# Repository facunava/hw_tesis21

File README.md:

View this project on [CADLAB.io](https://cadlab.io/project/24727). 

# hw_tesis21
Repositorio dedicado al desarrollo de hardware para la materia Proyecto final en Ingeniería Electrónica, en la casa de estudios Universidad Tecnológica Nacional Regional de Córdoba. [Grupo6/2021]

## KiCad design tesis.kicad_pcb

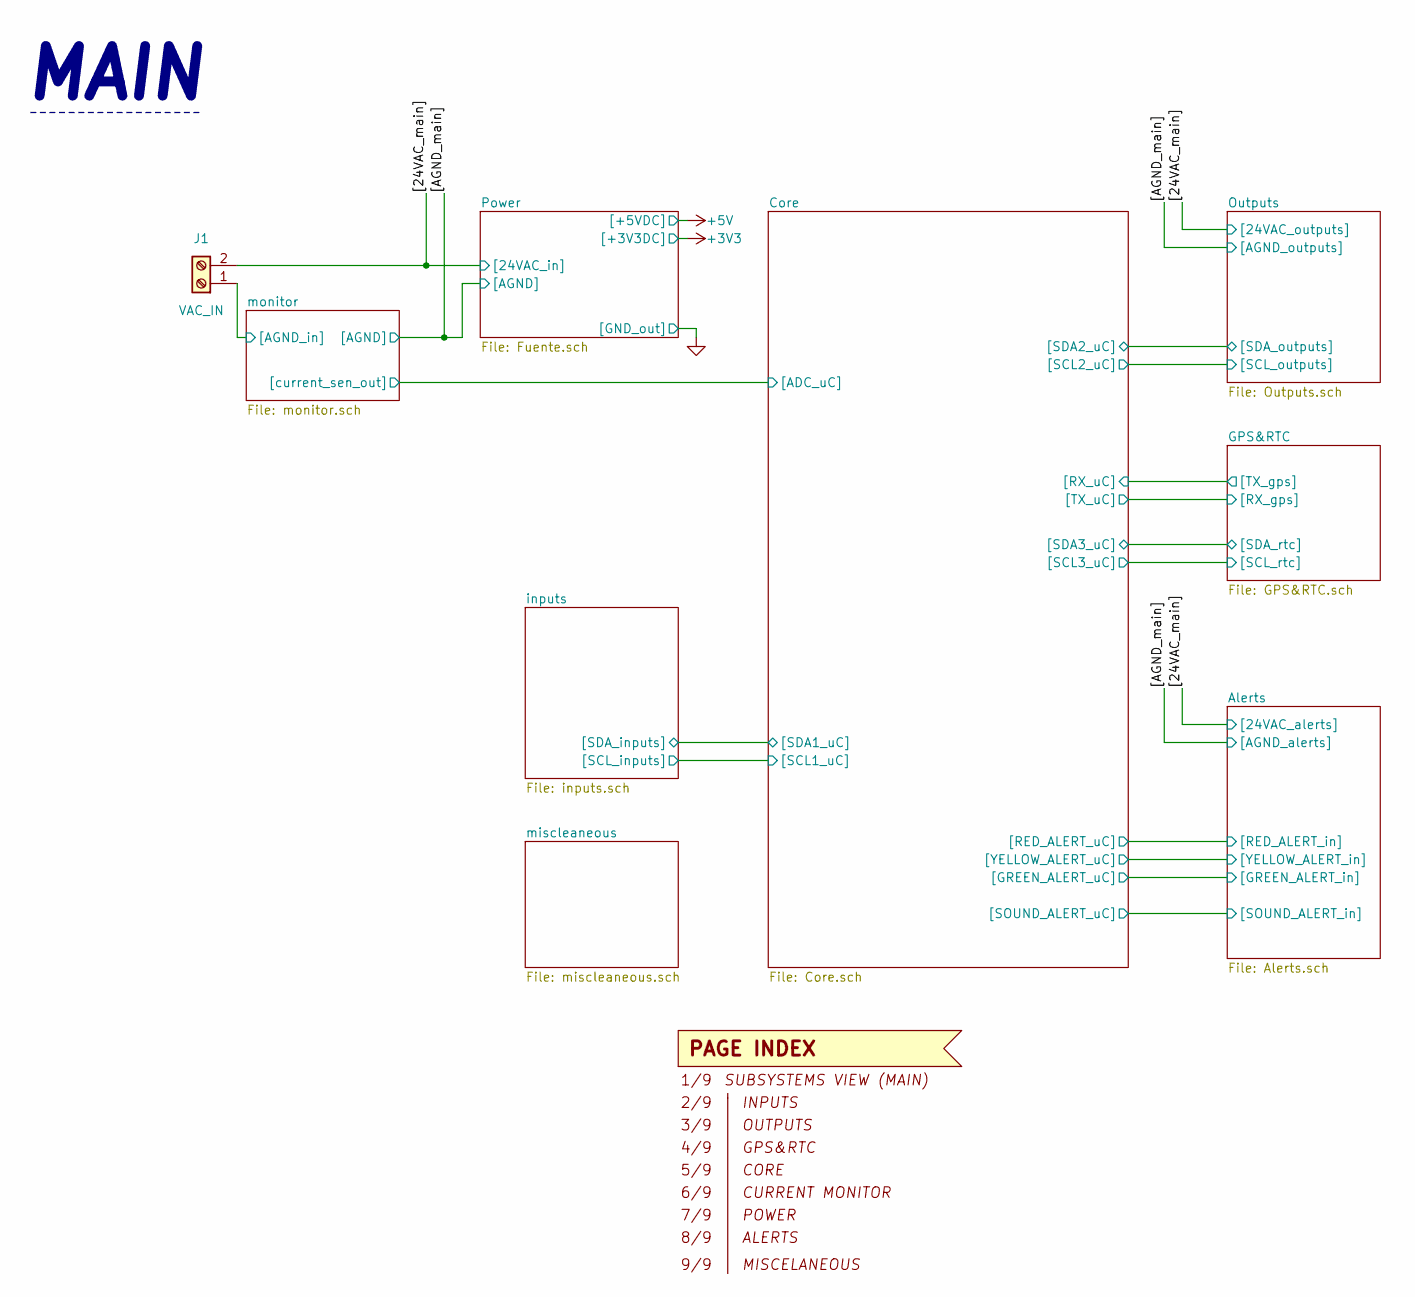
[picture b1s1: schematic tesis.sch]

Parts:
J1: VAC_IN; TerminalBlock_Phoenix_MKDS-1,5-2-5.08_1x02_P5.08mm_Horizont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

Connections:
/[24VAC_main]: J1.2; also elsewhere on the board
/monitor/[AGND_in]: J1.1; also elsewhere on the board

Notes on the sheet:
MAIN

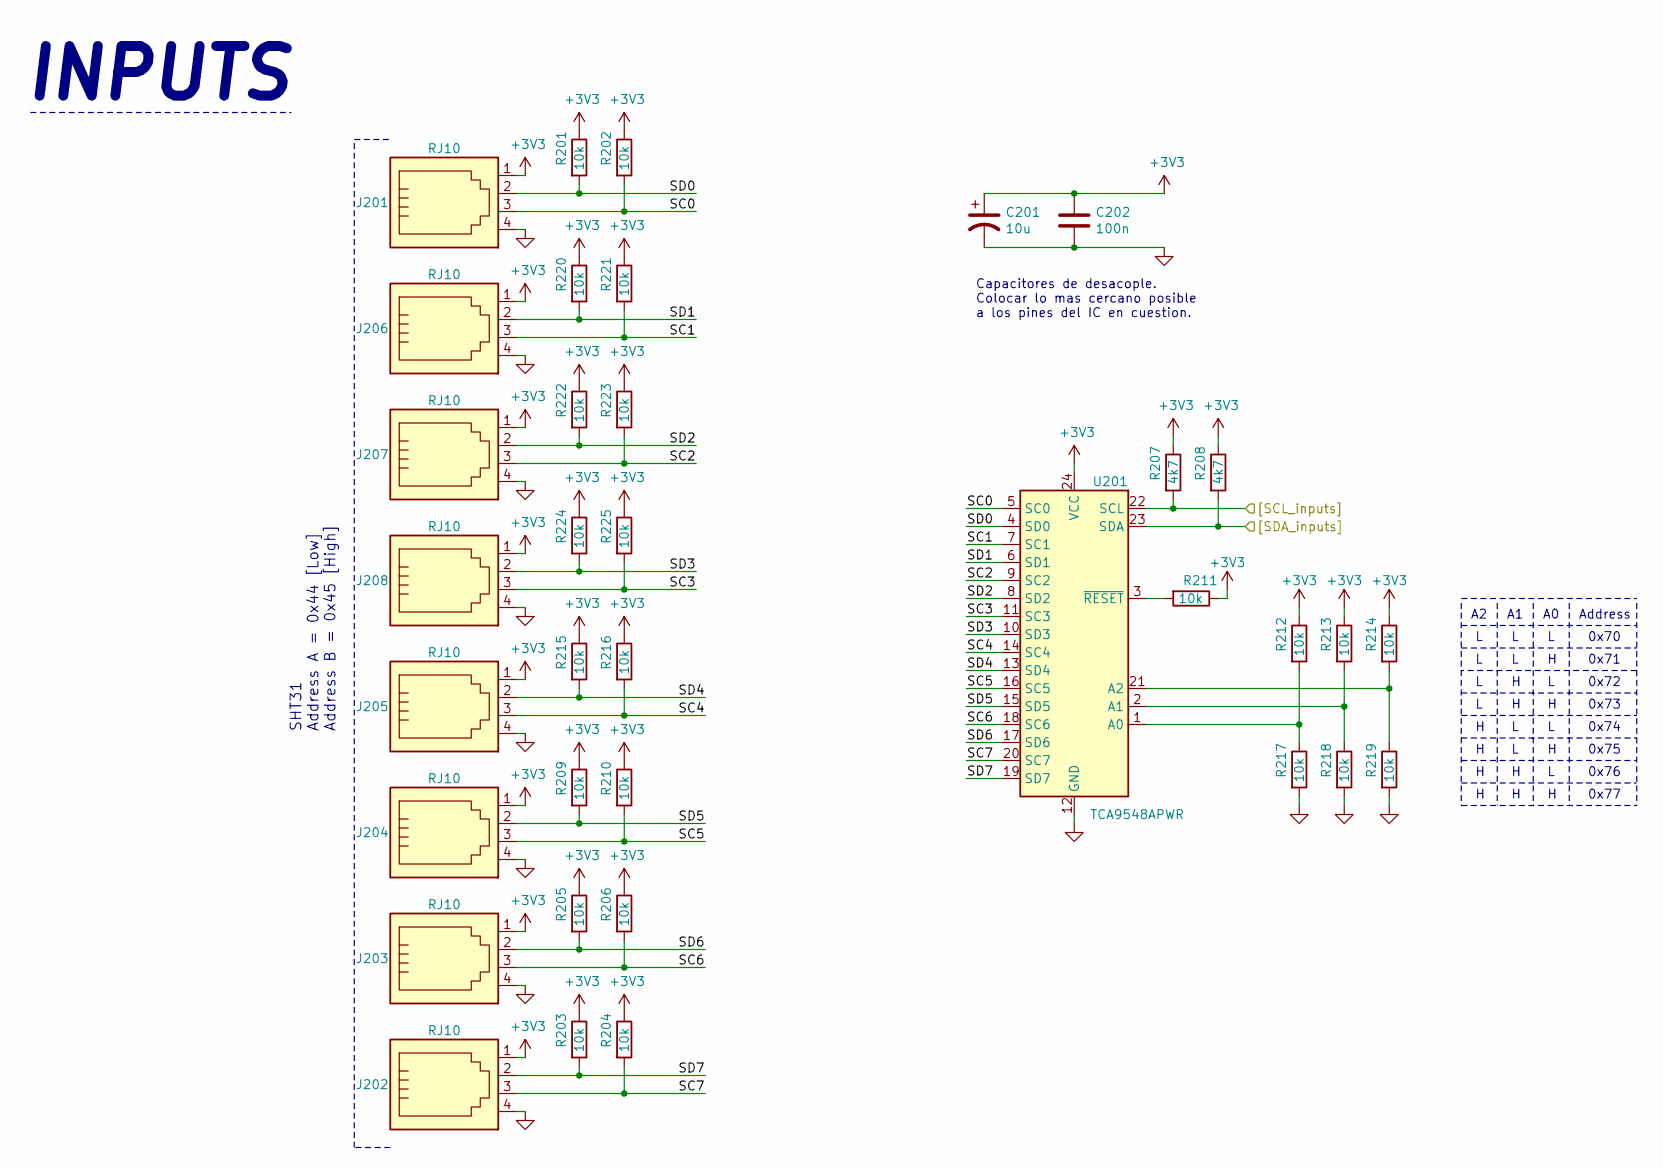
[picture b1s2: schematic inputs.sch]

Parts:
C201: 10u; C_0805_2012Metric_Pad1.18x1.45mm_HandSolder
C202: 100n; C_0805_2012Metric_Pad1.18x1.45mm_HandSolder
J201, J202, J203, J204, J205, J206, J207, J208: RJ10; 4P4C_narrow
R201, R202, R203, R204, R205, R206, R209, R210, R211, R212, R213, R214, R215, R216, R217, R218, R219, R220, R221, R222, R223, R224, R225: 10k; R_0805_2012Metric_Pad1.20x1.40mm_HandSolder
R207, R208: 4k7; R_0805_2012Metric_Pad1.20x1.40mm_HandSolder
U201: TCA9548APWR; TSSOP-24_4.4x7.8mm_P0.65mm

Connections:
+3V3: C201.1, C202.1, J201.1, J202.1, J203.1, J204.1, J205.1, J206.1, J207.1, J208.1, R201.1, R202.1, R203.1, R204.1, R205.1, R206.1, R207.1, R208.1, R209.1, R210.1, R211.1, R212.1, R213.1, R214.1, R215.1, R216.1, R220.1, R221.1, R222.1, R223.1, R224.1, R225.1, U201.24 (VCC); also elsewhere on the board
/Core/[SCL1_uC]: R207.2, U201.22 (SCL); also elsewhere on the board
/Core/[SDA1_uC]: R208.2, U201.23 (SDA); also elsewhere on the board
/inputs/SC0: J201.3, R202.2, U201.5 (SC0)
/inputs/SC1: J206.3, R221.2, U201.7 (SC1)
/inputs/SC2: J207.3, R223.2, U201.9 (SC2)
/inputs/SC3: J208.3, R225.2, U201.11 (SC3)
/inputs/SC4: J205.3, R216.2, U201.14 (SC4)
/inputs/SC5: J204.3, R210.2, U201.16 (SC5)
/inputs/SC6: J203.3, R206.2, U201.18 (SC6)
/inputs/SC7: J202.3, R204.2, U201.20 (SC7)
/inputs/SD0: J201.2, R201.2, U201.4 (SD0)
/inputs/SD1: J206.2, R220.2, U201.6 (SD1)
/inputs/SD2: J207.2, R222.2, U201.8 (SD2)
/inputs/SD3: J208.2, R224.2, U201.10 (SD3)
/inputs/SD4: J205.2, R215.2, U201.13 (SD4)
/inputs/SD5: J204.2, R209.2, U201.15 (SD5)
/inputs/SD6: J203.2, R205.2, U201.17 (SD6)
/inputs/SD7: J202.2, R203.2, U201.19 (SD7)
GND: C201.2, C202.2, J201.4, J202.4, J203.4, J204.4, J205.4, J206.4, J207.4, J208.4, R217.2, R218.2, R219.2, U201.12 (GND); also elsewhere on the board
unnamed: R211.2, U201.3 (~RESET)
unnamed: R212.2, R217.1, U201.1 (A0)
unnamed: R213.2, R218.1, U201.2 (A1)
unnamed: R214.2, R219.1, U201.21 (A2)

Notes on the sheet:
Address
0x70
0x71
0x72
0x73
0x74
0x75
0x76
0x77
SHT31 Address A = 0x44 [Low] Address B = 0x45 [High]
Capacitores de desacople. Colocar lo mas cercano posible a los pines del IC en cuestion.
INPUTS

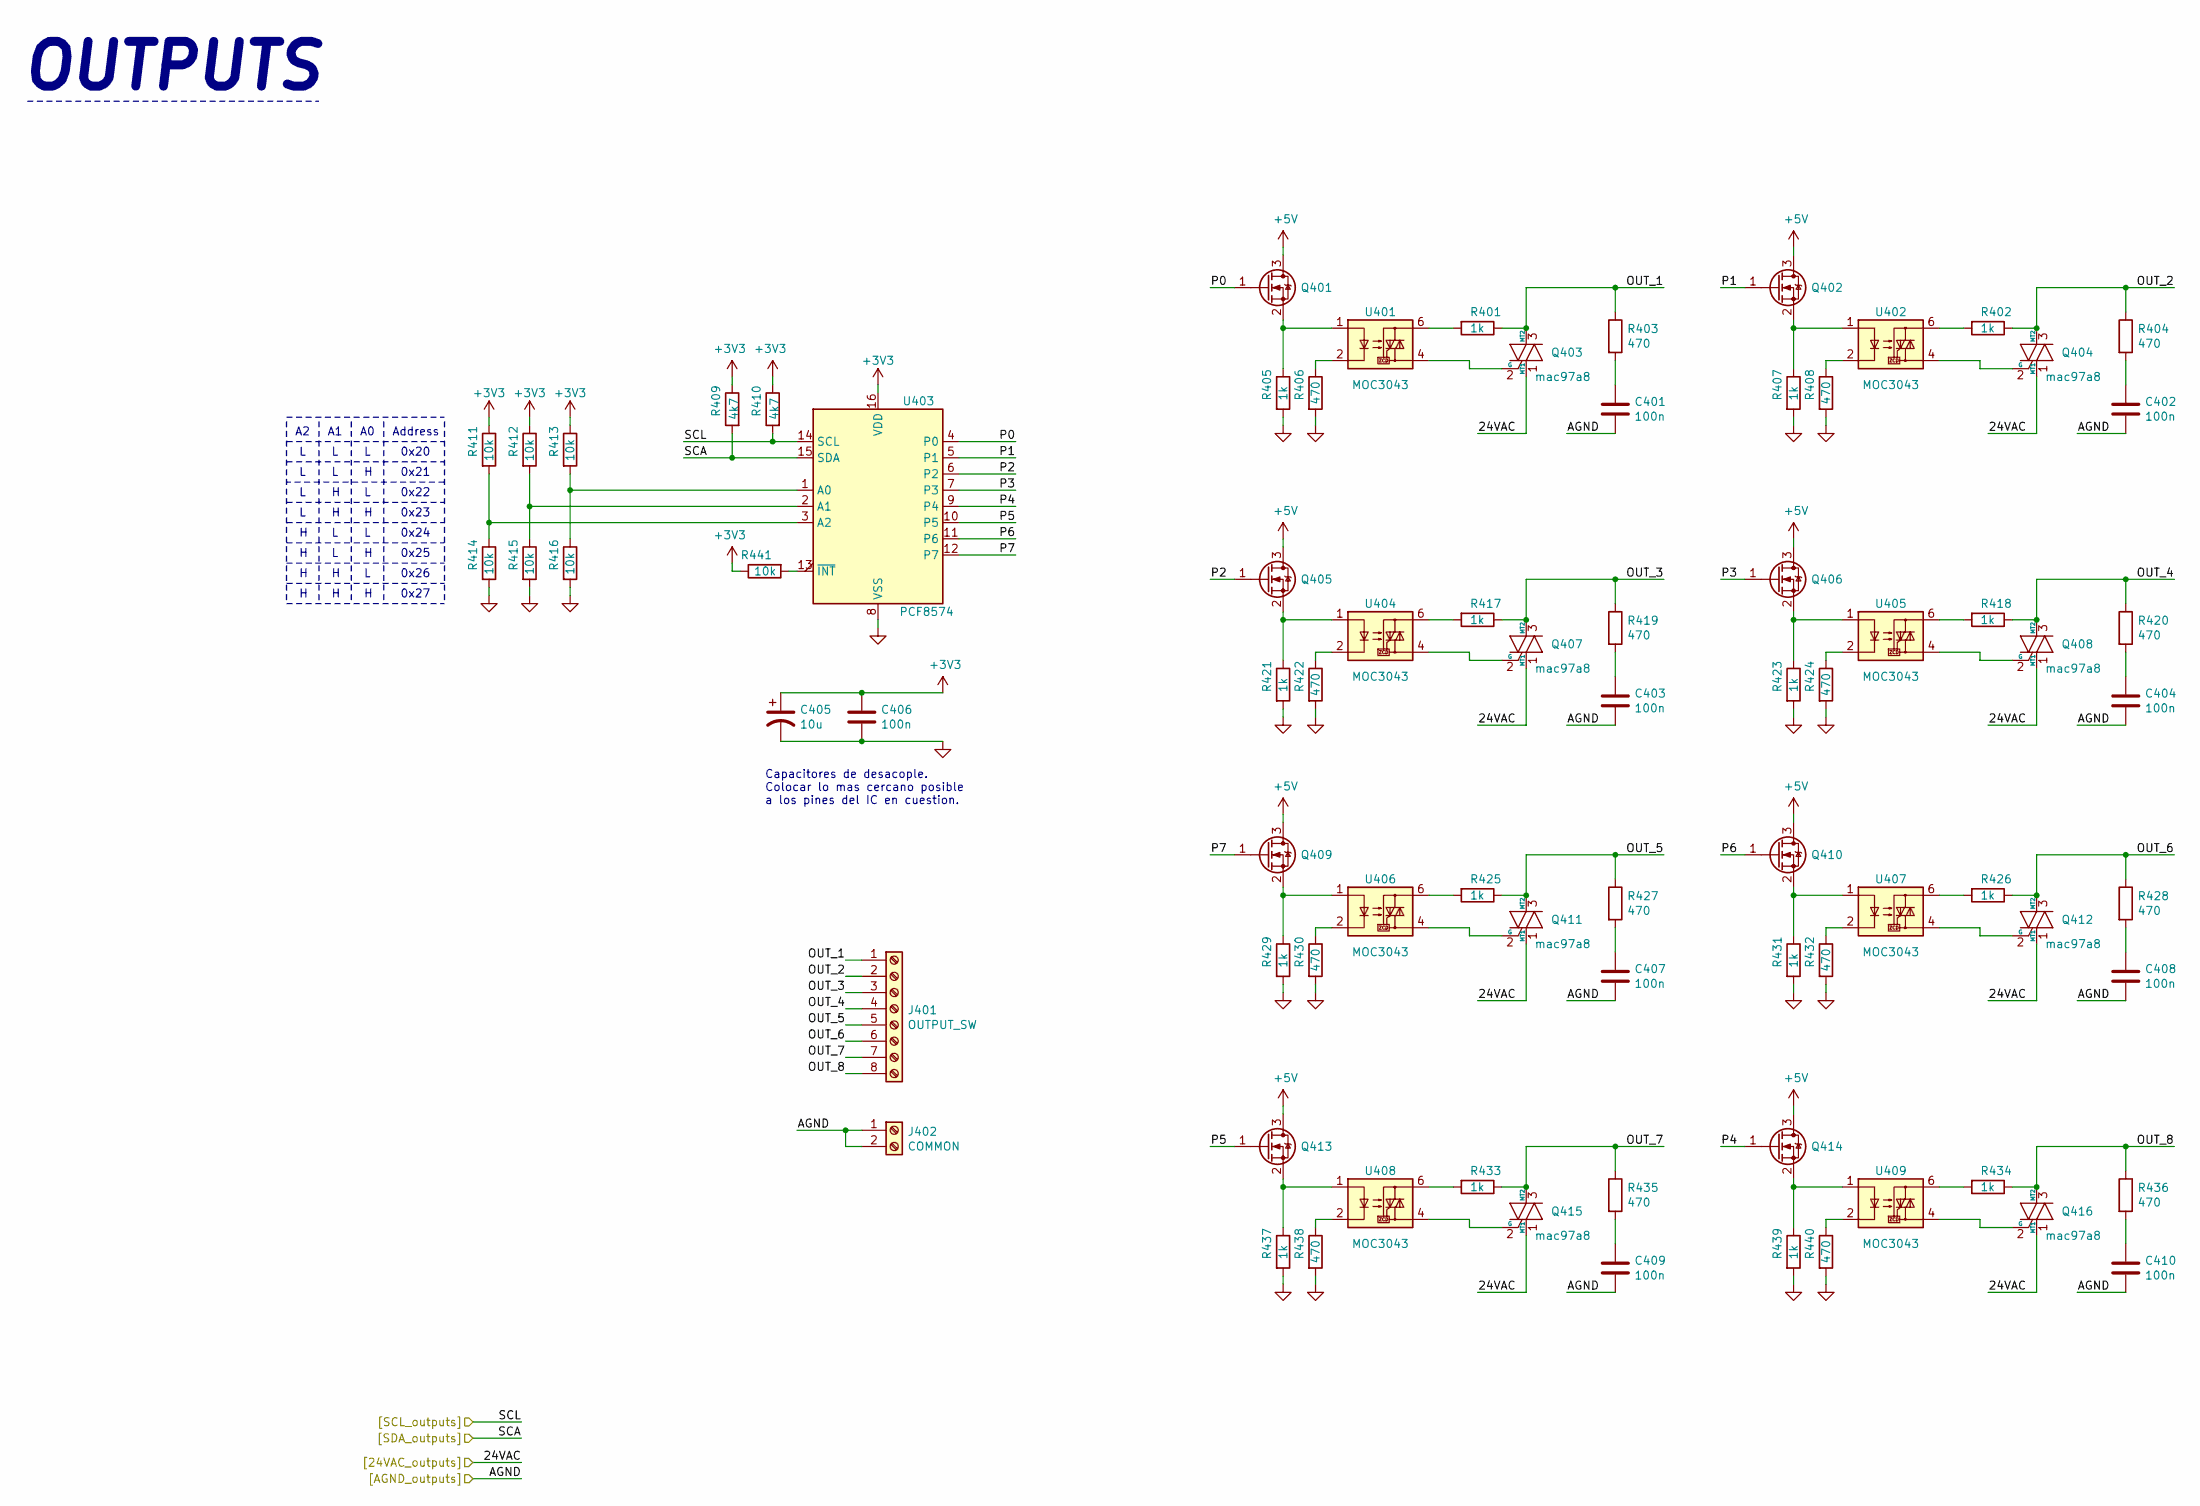
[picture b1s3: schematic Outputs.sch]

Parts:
C401, C402, C403, C404, C406, C407, C408, C409, C410: 100n; C_0805_2012Metric_Pad1.18x1.45mm_HandSolder
C405: 10u; C_0805_2012Metric_Pad1.18x1.45mm_HandSolder
J401: OUTPUT_SW; TerminalBlock_Phoenix_MKDS-1,5-8-5.08_1x08_P5.08mm_Horizont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
J402: COMMON; TerminalBlock_Phoenix_MKDS-1,5-2-5.08_1x02_P5.08mm_Horizont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
Q401, Q402, Q405, Q406, Q409, Q410, Q413, Q414: bss138; SOT-23
Q403, Q404, Q407, Q408, Q411, Q412, Q415, Q416: mac97a8; TO-92_Inline
R401, R402, R405, R407, R417, R418, R421, R423, R425, R426, R429, R431, R433, R434, R437, R439: 1k; R_0805_2012Metric_Pad1.20x1.40mm_HandSolder
R403, R404, R406, R408, R419, R420, R422, R424, R427, R428, R430, R432, R435, R436, R438, R440: 470; R_0805_2012Metric_Pad1.20x1.40mm_HandSolder
R409, R410: 4k7; R_0805_2012Metric_Pad1.20x1.40mm_HandSolder
R411, R412, R413, R414, R415, R416, R441: 10k; R_0805_2012Metric_Pad1.20x1.40mm_HandSolder
U401, U402, U404, U405, U406, U407, U408, U409: MOC3043; DIP-6_W7.62mm_LongPads
U403: PCF8574; SOIC-16W_7.5x10.3mm_P1.27mm

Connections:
+3V3: C405.1, C406.1, R409.1, R410.1, R411.1, R412.1, R413.1, R441.1, U403.16 (VDD); also elsewhere on the board
+5V: Q401.3 (D), Q402.3 (D), Q405.3 (D), Q406.3 (D), Q409.3 (D), Q410.3 (D), Q413.3 (D), Q414.3 (D); also elsewhere on the board
/Core/[SCL2_uC]: R410.2, U403.14 (SCL); also elsewhere on the board
/Core/[SDA2_uC]: R409.2, U403.15 (SDA); also elsewhere on the board
/Outputs/OUT_1: J401.1, Q403.3 (MT2), R401.1, R403.1
/Outputs/OUT_2: J401.2, Q404.3 (MT2), R402.1, R404.1
/Outputs/OUT_3: J401.3, Q407.3 (MT2), R417.1, R419.1
/Outputs/OUT_4: J401.4, Q408.3 (MT2), R418.1, R420.1
/Outputs/OUT_5: J401.5, Q411.3 (MT2), R425.1, R427.1
/Outputs/OUT_6: J401.6, Q412.3 (MT2), R426.1, R428.1
/Outputs/OUT_7: J401.7, Q415.3 (MT2), R433.1, R435.1
/Outputs/OUT_8: J401.8, Q416.3 (MT2), R434.1, R436.1
/Outputs/P0: Q401.1 (G), U403.4 (P0)
/Outputs/P1: Q402.1 (G), U403.5 (P1)
/Outputs/P2: Q405.1 (G), U403.6 (P2)
/Outputs/P3: Q406.1 (G), U403.7 (P3)
/Outputs/P4: Q414.1 (G), U403.9 (P4)
/Outputs/P5: Q413.1 (G), U403.10 (P5)
/Outputs/P6: Q410.1 (G), U403.11 (P6)
/Outputs/P7: Q409.1 (G), U403.12 (P7)
/[24VAC_main]: Q403.1 (MT1), Q404.1 (MT1), Q407.1 (MT1), Q408.1 (MT1), Q411.1 (MT1), Q412.1 (MT1), Q415.1 (MT1), Q416.1 (MT1); also elsewhere on the board
/[AGND_main]: C401.2, C402.2, C403.2, C404.2, C407.2, C408.2, C409.2, C410.2, J402.1, J402.2; also elsewhere on the board
GND: C405.2, C406.2, R405.2, R406.2, R407.2, R408.2, R414.2, R415.2, R416.2, R421.2, R422.2, R423.2, R424.2, R429.2, R430.2, R431.2, R432.2, R437.2, R438.2, R439.2, R440.2, U403.8 (VSS); also elsewhere on the board
unnamed: C401.1, R403.2
unnamed: C402.1, R404.2
unnamed: C403.1, R419.2
unnamed: C404.1, R420.2
unnamed: C407.1, R427.2
unnamed: C408.1, R428.2
unnamed: C409.1, R435.2
unnamed: C410.1, R436.2
unnamed: Q401.2 (S), R405.1, U401.1
unnamed: Q402.2 (S), R407.1, U402.1
unnamed: Q403.2 (G), U401.4
unnamed: Q404.2 (G), U402.4
unnamed: Q405.2 (S), R421.1, U404.1
unnamed: Q406.2 (S), R423.1, U405.1
unnamed: Q407.2 (G), U404.4
unnamed: Q408.2 (G), U405.4
unnamed: Q409.2 (S), R429.1, U406.1
unnamed: Q410.2 (S), R431.1, U407.1
unnamed: Q411.2 (G), U406.4
unnamed: Q412.2 (G), U407.4
unnamed: Q413.2 (S), R437.1, U408.1
unnamed: Q414.2 (S), R439.1, U409.1
unnamed: Q415.2 (G), U408.4
unnamed: Q416.2 (G), U409.4
unnamed: R401.2, U401.6
unnamed: R402.2, U402.6
unnamed: R406.1, U401.2
unnamed: R408.1, U402.2
unnamed: R411.2, R414.1, U403.3 (A2)
unnamed: R412.2, R415.1, U403.2 (A1)
unnamed: R413.2, R416.1, U403.1 (A0)
unnamed: R417.2, U404.6
unnamed: R418.2, U405.6
unnamed: R422.1, U404.2
unnamed: R424.1, U405.2
unnamed: R425.2, U406.6
unnamed: R426.2, U407.6
unnamed: R430.1, U406.2
unnamed: R432.1, U407.2
unnamed: R433.2, U408.6
unnamed: R434.2, U409.6
unnamed: R438.1, U408.2
unnamed: R440.1, U409.2
unnamed: R441.2, U403.13 (~INT~)

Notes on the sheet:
Capacitores de desacople. Colocar lo mas cercano posible a los pines del IC en cuestion.
Address
0x20
0x21
0x22
0x23
0x24
0x25
0x26
0x27
OUTPUTS

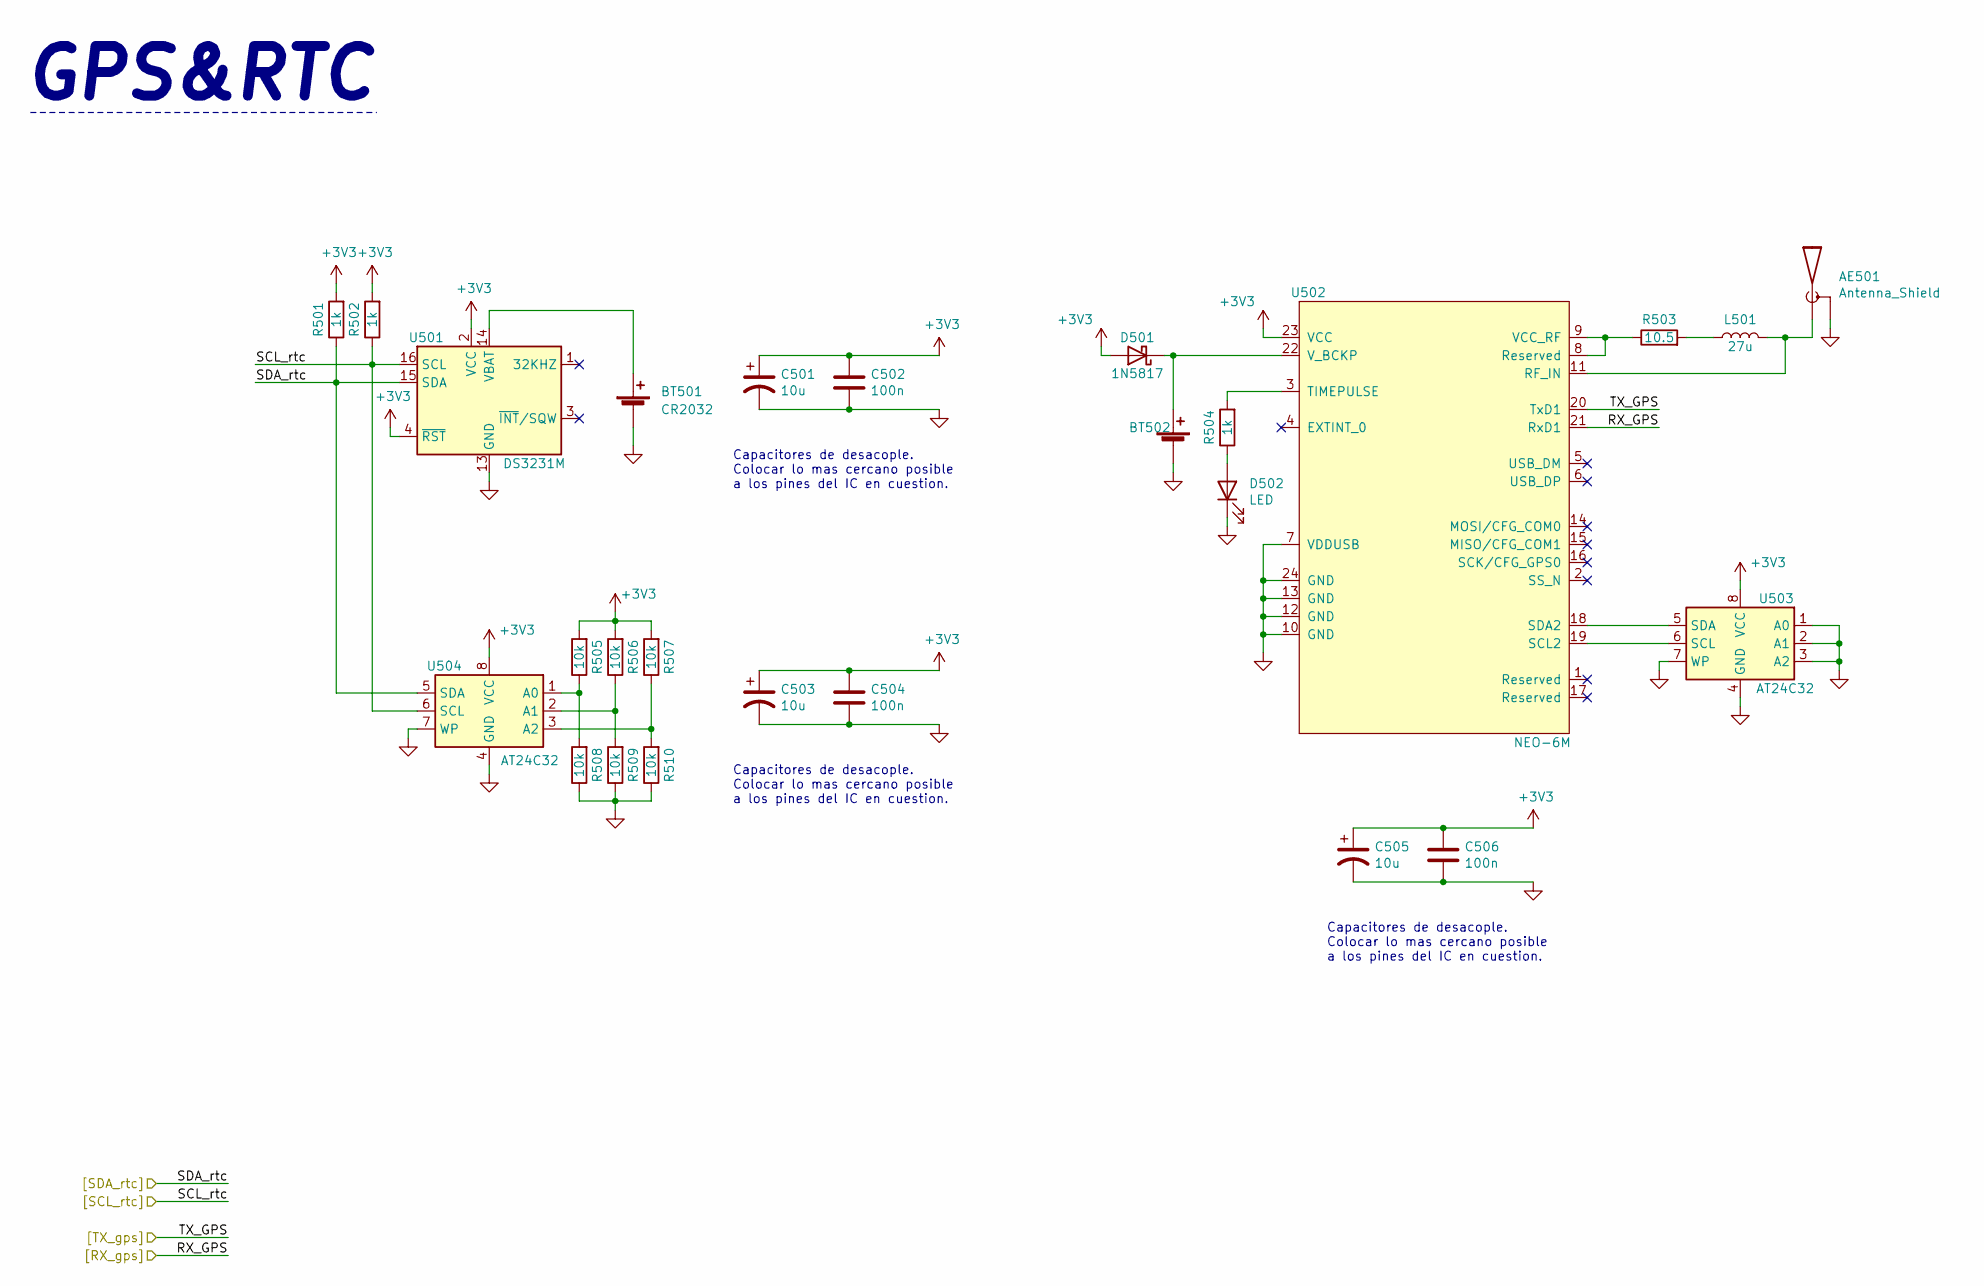
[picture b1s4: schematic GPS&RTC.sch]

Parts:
AE501: Antenna_Shield; U.FL_Molex_MCRF_73412-0110_Vertical
BT501: CR2032; BatteryHolder_ComfortableElectronic_CH273-2450_1x2450
BT502: Battery_Cell; BatteryHolder_Seiko_MS621F
C501, C503, C505: 10u; C_0805_2012Metric_Pad1.18x1.45mm_HandSolder
C502, C504, C506: 100n; C_0805_2012Metric_Pad1.18x1.45mm_HandSolder
D501: 1N5817; D_MiniMELF_Handsoldering
D502: LED; LED_0805_2012Metric_Castellated
L501: 27u; L_0805_2012Metric_Pad1.15x1.40mm_HandSolder
R501, R502, R504: 1k; R_0805_2012Metric_Pad1.20x1.40mm_HandSolder
R503: 10.5; R_0805_2012Metric_Pad1.20x1.40mm_HandSolder
R505, R506, R507, R508, R509, R510: 10k; R_0805_2012Metric_Pad1.20x1.40mm_HandSolder
U501: DS3231M; SOIC-16W_7.5x10.3mm_P1.27mm
U502: NEO-6M; ublox_NEO
U503: AT24C32; TSSOP-8_4.4x3mm_P0.65mm
U504: AT24C32; SOIC-8_3.9x4.9mm_P1.27mm

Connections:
+3V3: C501.1, C502.1, C503.1, C504.1, C505.1, C506.1, D501.2 (A), R501.2, R502.2, R505.2, R506.2, R507.2, U501.2 (VCC), U501.4 (~RST), U502.23 (VCC), U503.8 (VCC), U504.8 (VCC); also elsewhere on the board
/Core/[RX_uC]: U502.20 (TxD1); also elsewhere on the board
/Core/[SCL3_uC]: R502.1, U501.16 (SCL), U504.6 (SCL); also elsewhere on the board
/Core/[SDA3_uC]: R501.1, U501.15 (SDA), U504.5 (SDA); also elsewhere on the board
/GPS&RTC/[RX_gps]: U502.21 (RxD1); also elsewhere on the board
GND: AE501.2 (Shield), BT501.2 (-), BT502.2 (-), C501.2, C502.2, C503.2, C504.2, C505.2, C506.2, D502.1 (K), R508.1, R509.1, R510.1, U501.5 (GND), U501.6 (GND), U501.7 (GND), U501.8 (GND), U501.9 (GND), U501.10 (GND), U501.11 (GND), U501.12 (GND), U501.13 (GND), U502.7 (VDDUSB), U502.10 (GND), U502.12 (GND), U502.13 (GND), U502.24 (GND), U503.1 (A0), U503.2 (A1), U503.3 (A2), U503.4 (GND), U503.7 (WP), U504.4 (GND), U504.7 (WP); also elsewhere on the board
unnamed: AE501.1 (A), L501.2, U502.11 (RF_IN)
unnamed: BT501.1 (+), U501.14 (VBAT)
unnamed: BT502.1 (+), D501.1 (K), U502.22 (V_BCKP)
unnamed: D502.2 (A), R504.1
unnamed: L501.1, R503.2
unnamed: R503.1, U502.8 (Reserved), U502.9 (VCC_RF)
unnamed: R504.2, U502.3 (TIMEPULSE)
unnamed: R505.1, R508.2, U504.1 (A0)
unnamed: R506.1, R509.2, U504.2 (A1)
unnamed: R507.1, R510.2, U504.3 (A2)
unnamed: U502.18 (SDA2), U503.5 (SDA)
unnamed: U502.19 (SCL2), U503.6 (SCL)

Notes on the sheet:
Capacitores de desacople. Colocar lo mas cercano posible a los pines del IC en cuestion.
GPS&RTC

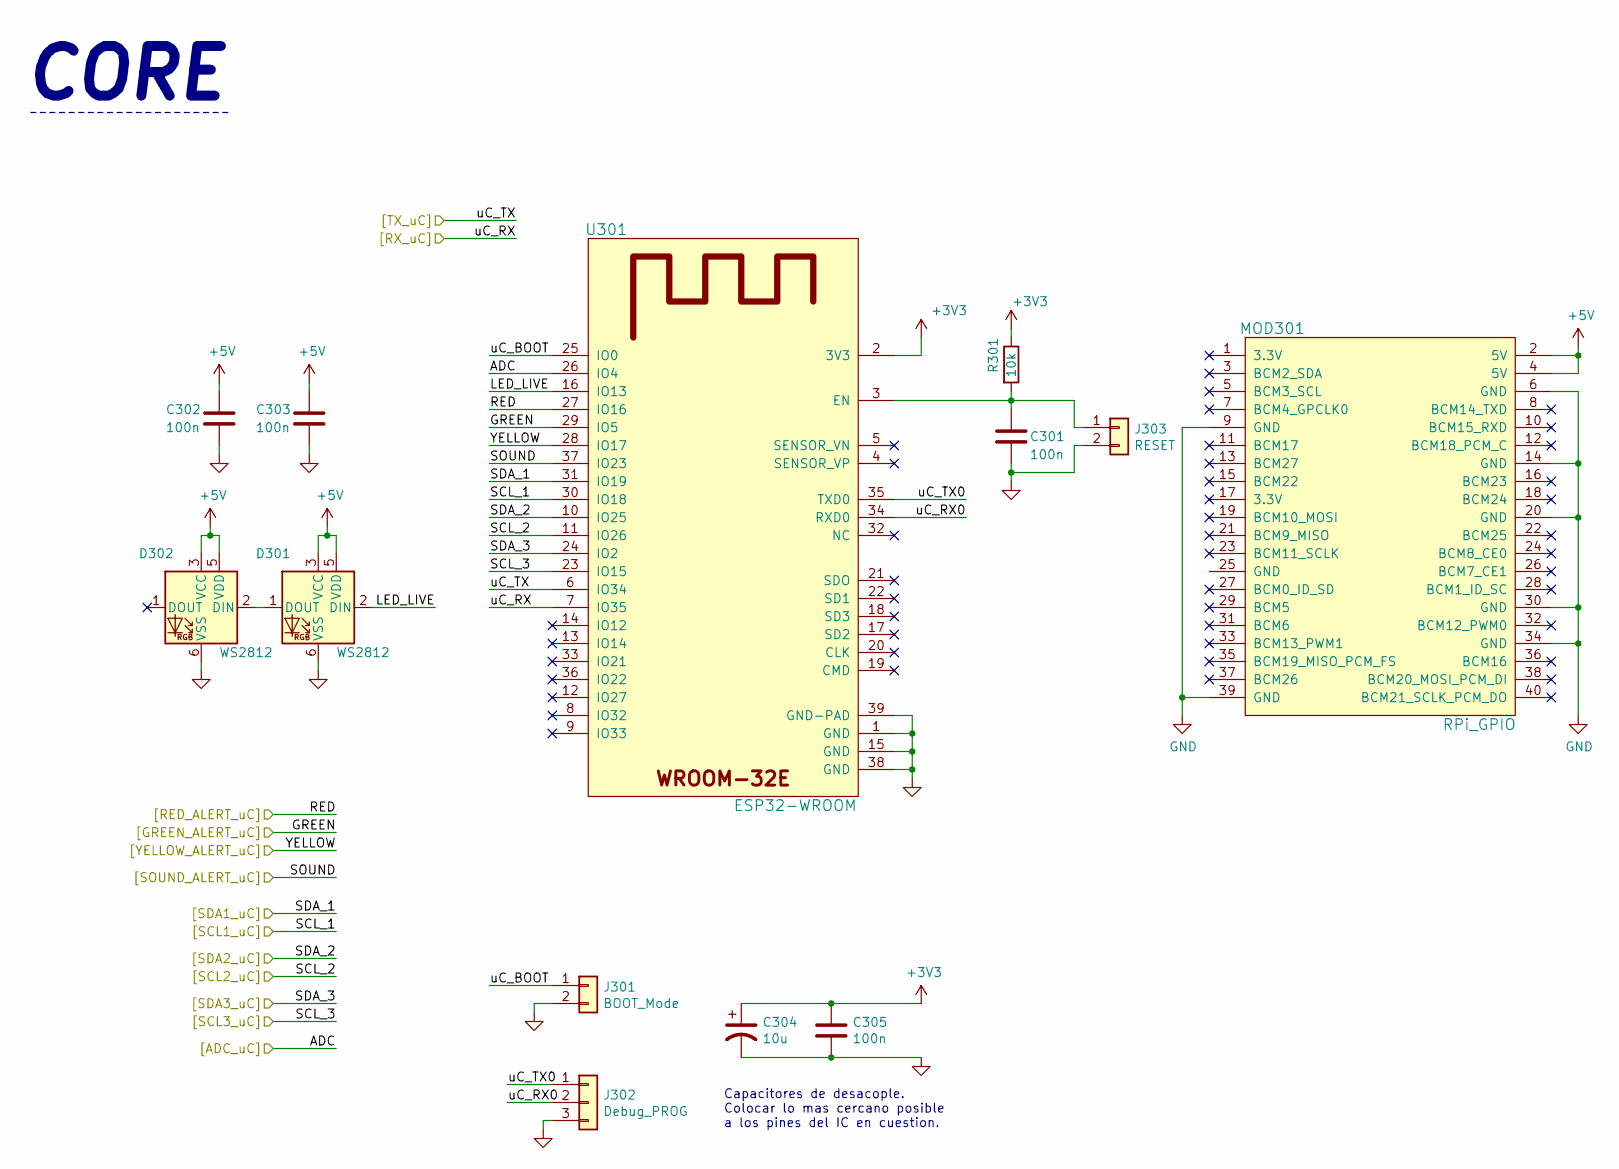
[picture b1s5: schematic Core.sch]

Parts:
C301, C302, C303, C305: 100n; C_0805_2012Metric_Pad1.18x1.45mm_HandSolder
C304: 10u; C_0805_2012Metric_Pad1.18x1.45mm_HandSolder
D301, D302: WS2812; LED_WS2812_PLCC6_5.0x5.0mm_P1.6mm
J301: BOOT_Mode; PinHeader_1x02_P2.54mm_Vertical
J302: Debug_PROG; PinHeader_1x03_P2.54mm_Vertical
J303: RESET; PinHeader_1x02_P2.54mm_Vertical
MOD301: RPi_GPIO; PinSocket_2x20_P2.54mm_Vertical_SMD
R301: 10k; R_0805_2012Metric_Pad1.20x1.40mm_HandSolder
U301: ESP32-WROOM

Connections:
+3V3: C304.1, C305.1, R301.1, U301.2 (3V3); also elsewhere on the board
+5V: C302.1, C303.1, D301.3 (VCC), D301.5 (VDD), D302.3 (VCC), D302.5 (VDD), MOD301.2 (5V), MOD301.4 (5V); also elsewhere on the board
/Alerts/[GREEN_ALERT_in]: U301.29 (IO5); also elsewhere on the board
/Alerts/[RED_ALERT_in]: U301.27 (IO16); also elsewhere on the board
/Alerts/[SOUND_ALERT_in]: U301.37 (IO23); also elsewhere on the board
/Alerts/[YELLOW_ALERT_in]: U301.28 (IO17); also elsewhere on the board
/Core/LED_LIVE: D301.2 (DIN), U301.16 (IO13)
/Core/[ADC_uC]: U301.26 (IO4); also elsewhere on the board
/Core/[RX_uC]: U301.7 (IO35); also elsewhere on the board
/Core/[SCL1_uC]: U301.30 (IO18); also elsewhere on the board
/Core/[SCL2_uC]: U301.11 (IO26); also elsewhere on the board
/Core/[SCL3_uC]: U301.23 (IO15); also elsewhere on the board
/Core/[SDA1_uC]: U301.31 (IO19); also elsewhere on the board
/Core/[SDA2_uC]: U301.10 (IO25); also elsewhere on the board
/Core/[SDA3_uC]: U301.24 (IO2); also elsewhere on the board
/Core/uC_BOOT: J301.1, U301.25 (IO0)
/Core/uC_RX0: J302.2, U301.34 (RXD0)
/Core/uC_TX0: J302.1, U301.35 (TXD0)
/GPS&RTC/[RX_gps]: U301.6 (IO34); also elsewhere on the board
GND: C301.2, C302.2, C303.2, C304.2, C305.2, D301.6 (VSS), D302.6 (VSS), J301.2, J302.3, J303.2, MOD301.6 (GND), MOD301.9 (GND), MOD301.14 (GND), MOD301.20 (GND), MOD301.30 (GND), MOD301.34 (GND), MOD301.39 (GND), U301.1 (GND), U301.15 (GND), U301.38 (GND), U301.39 (GND-PAD); also elsewhere on the board
unnamed: C301.1, J303.1, R301.2, U301.3 (EN)
unnamed: D301.1 (DOUT), D302.2 (DIN)

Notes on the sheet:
Capacitores de desacople. Colocar lo mas cercano posible a los pines del IC en cuestion.
CORE

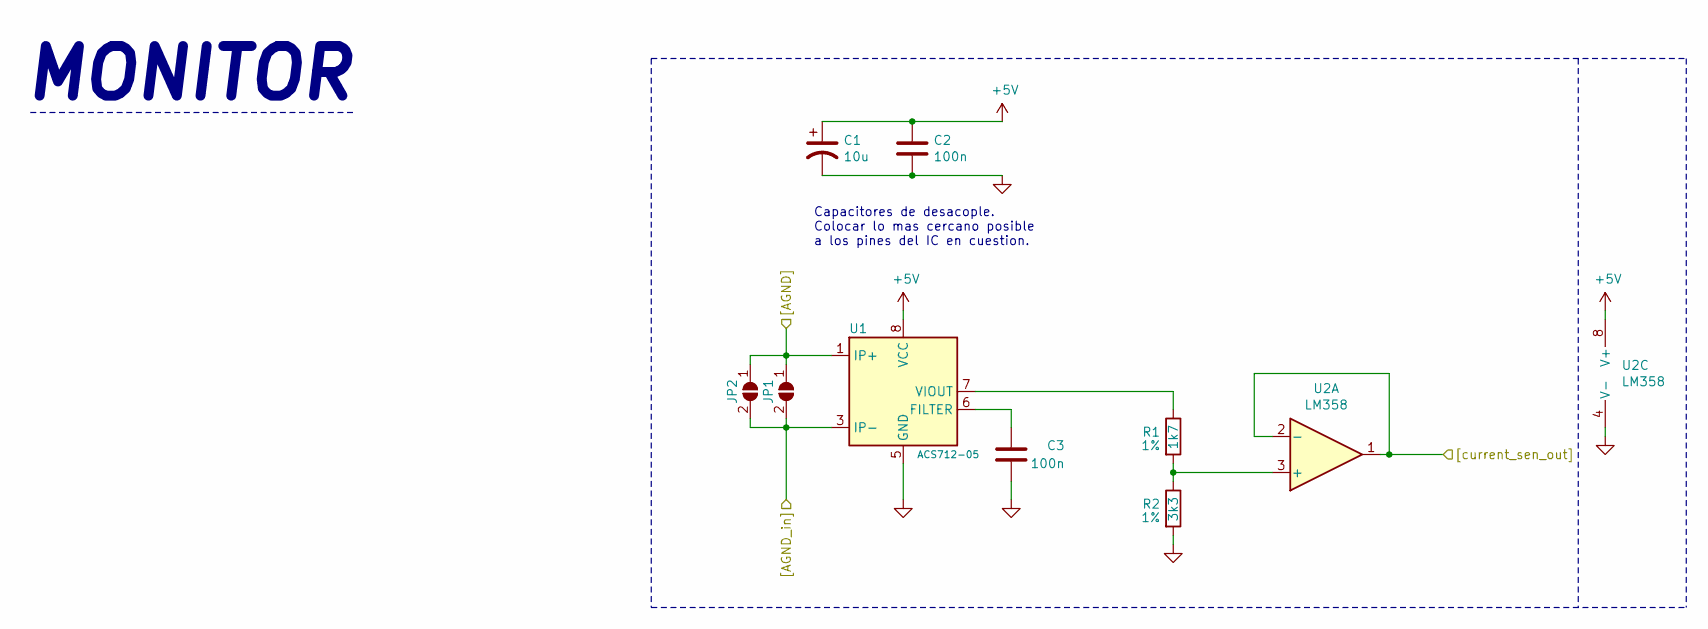
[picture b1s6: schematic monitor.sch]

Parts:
C1: 10u; C_0805_2012Metric_Pad1.18x1.45mm_HandSolder
C2, C3: 100n; C_0805_2012Metric_Pad1.18x1.45mm_HandSolder
JP1, JP2: jumper; SolderJumper-2_P1.3mm_Open_RoundedPad1.0x1.5mm
R1: 1k7; R_0805_2012Metric_Pad1.20x1.40mm_HandSolder
R2: 3k3; R_0805_2012Metric_Pad1.20x1.40mm_HandSolder
U1: ACS712-05; SOIC-8_3.9x4.9mm_P1.27mm
U2: LM358; SOIC-8_3.9x4.9mm_P1.27mm

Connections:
+5V: C1.1, C2.1, U1.8 (VCC), U2.8 (V+); also elsewhere on the board
/Core/[ADC_uC]: U2.1, U2.2 (-); also elsewhere on the board
/[AGND_main]: JP1.1 (A), JP2.1 (A), U1.1 (IP+), U1.2 (IP+); also elsewhere on the board
/monitor/[AGND_in]: JP1.2 (B), JP2.2 (B), U1.3 (IP-), U1.4 (IP-); also elsewhere on the board
GND: C1.2, C2.2, C3.2, R2.2, U1.5 (GND), U2.4 (V-); also elsewhere on the board
unnamed: C3.1, U1.6 (FILTER)
unnamed: R1.1, U1.7 (VIOUT)
unnamed: R1.2, R2.1, U2.3 (+)

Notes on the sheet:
Capacitores de desacople. Colocar lo mas cercano posible a los pines del IC en cuestion.
MONITOR
